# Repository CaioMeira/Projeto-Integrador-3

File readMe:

# Projeto Integrador III - Braço Robótico

## Descrição do Projeto
Repositório destinado ao desenvolvimento do **Projeto Integrador III** do curso de Engenharia Eletrônica.  
O projeto consiste na construção de um **braço robótico controlado por ESP32**, integrando **ROS** e simulações no **Gazebo**.

## Equipe
- Caio Neves Meira
- Guilherme da Costa Franco
- Marcelo Zampieri Pereira da Silva  

Professores Orientadores: Matheus Leitzke Pinto e Renan Augusto Starke

---

<p align=center><strong>SUMÁRIO</strong></p>

[**1. ANÁLISE**](./analise.md)<br>
[**2. PROJETO**](./projeto.md)<br>
[**3. IMPLEMENTAÇÃO (ESP32 + ROS)**](./implementacao.md)<br>
[**4. TESTES e SIMULAÇÕES**](./testes.md)<br>

---

## Tecnologias Utilizadas
- ESP32
- Servomotores SG90, HX5010, HK15328D
- ROS (Robot Operating System)
- Gazebo (simulação 3D)

## Objetivo
Desenvolver um braço robótico funcional capaz de ser controlado via ESP32, com suporte à integração no ROS e validação em ambiente de simulação.

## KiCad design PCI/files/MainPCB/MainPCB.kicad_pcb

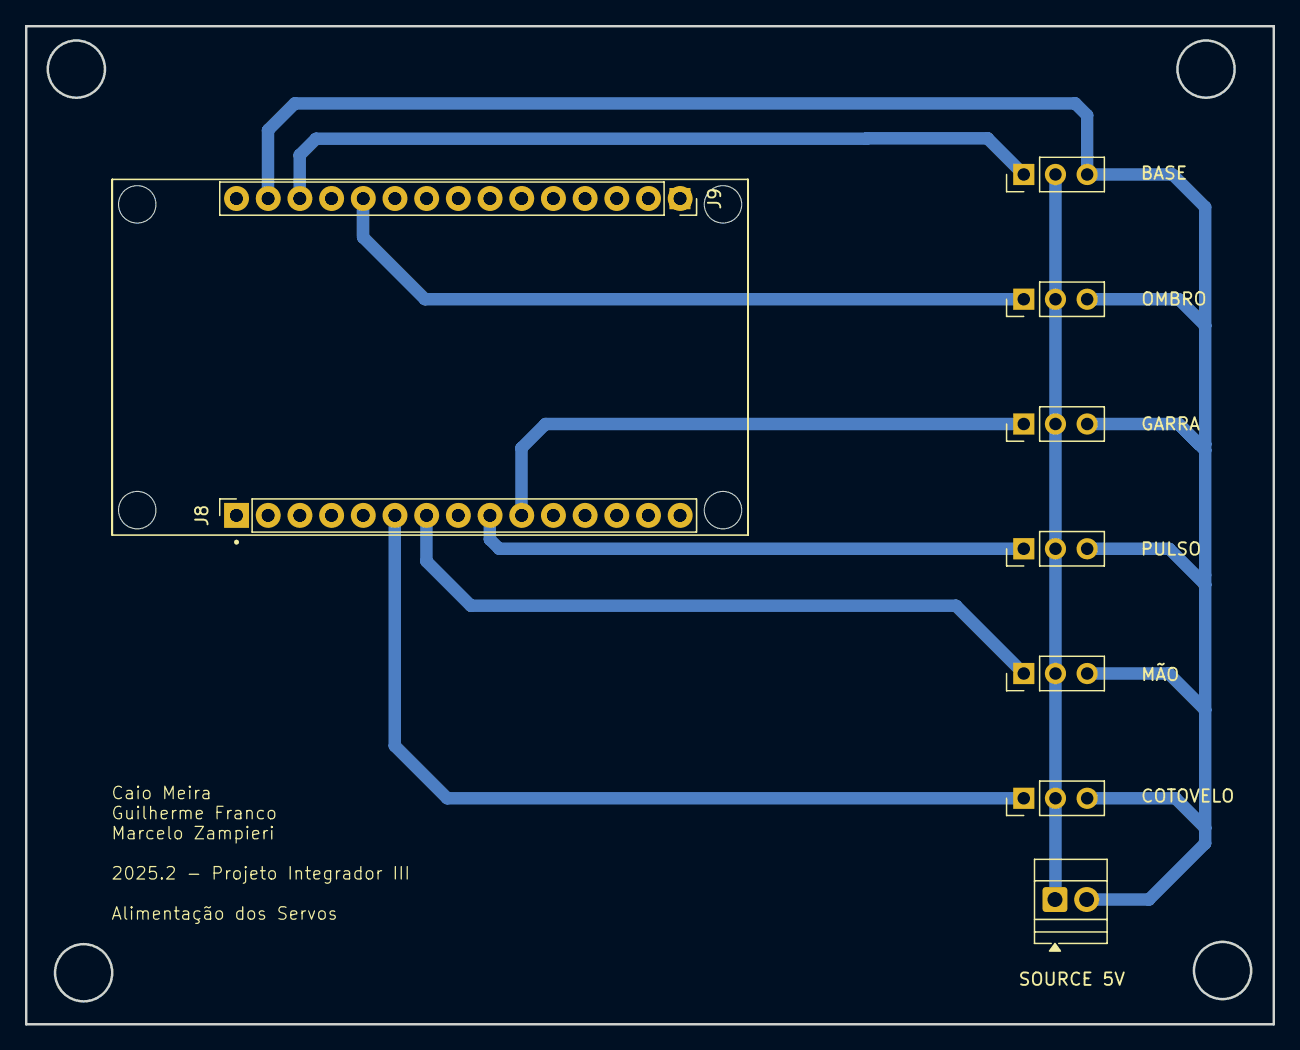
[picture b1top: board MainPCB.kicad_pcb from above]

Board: 2 copper layers, 100.0 x 80.0 mm, 9 parts (0 on the bottom side), 8 nets.

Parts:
BASE: Conn_01x03_Pin; PinHeader_1x03_P2.54mm_Vertical
COTOVELO: Conn_01x03_Pin; PinHeader_1x03_P2.54mm_Vertical
GARRA: Conn_01x03_Pin; PinHeader_1x03_P2.54mm_Vertical
J8, J9: Conn_01x15_Socket; PinSocket_1x15_P2.54mm_Vertical
MÃO: Conn_01x03_Pin; PinHeader_1x03_P2.54mm_Vertical
OMBRO: Conn_01x03_Pin; PinHeader_1x03_P2.54mm_Vertical
PULSO: Conn_01x03_Pin; PinHeader_1x03_P2.54mm_Vertical
SOURCE 5V: Screw_Terminal_01x02; TerminalBlock_Xinya_XY308-2.54-2P_1x02_P2.54mm_Horizontal

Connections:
unnamed: J9.11, OMBRO.1
unnamed: BASE.2, COTOVELO.2, GARRA.2, MÃO.2, OMBRO.2, PULSO.2, SOURCE 5V.1
unnamed: BASE.3, COTOVELO.3, GARRA.3, J9.14, MÃO.3, OMBRO.3, PULSO.3, SOURCE 5V.2
unnamed: GARRA.1, J8.10
unnamed: J8.9, PULSO.1
unnamed: J8.7, MÃO.1
unnamed: BASE.1, J9.13
unnamed: COTOVELO.1, J8.6

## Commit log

2025-09-25 Adicionando banco de imagens na raiz do repo
2025-09-25 Rename readMe to readMe.md
2025-09-25 Teste de commit no vscode recem configurado
2025-09-25 Update componentes.md
    Adicionando campo de impactos do consumo de corrente dos servos motores.
2025-10-25 Update robotic_arm.cpp
    Adicionando:
    - Controle suave de PWM (default ou custom)
    - Função de ações concorrentes
    - Comentários
2025-10-25 Rename robotic_arm.cpp to [LEGACY]robotic_arm.cpp
    Alterando nome do arquivo original para servir de backtrack no futuro, pois esse código será refatorado para melhorar a leitura e debug posteriormente
2025-10-25 Modularizando código legado
2025-10-29 Adicionando novos arquivos
    Foram criados o sequencer e o macro manager para possibilitar o carregamento fluido das poses e, assim, criar uma sequência de movimentos pré definidos.
2025-10-29 Update CommandParser.cpp
    Implementando função para mover todos os servos ao mesmo tempo
2025-11-27 Implementação do ROS e fixes de performance
2025-11-27 Adicionado guia de utilização ROS e melhoria da documentação
2025-12-18 Port de ROS com script em python
2025-12-18 Ajuste de documentação geral
2025-12-18 Update readMe.md
    Arrumando o path do IntegraçãoROS.md
2025-12-18 Add initial project description for robotic arm
2025-12-18 Revise project structure and arm specifications
    Redefine project structure and update robotic arm details.
2025-12-18 Fix table formatting in braco.md
2025-12-18 Rename interface.jpg to userview.jpg
